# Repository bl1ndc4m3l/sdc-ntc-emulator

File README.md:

# SDC NTC emulator

A wireless room sensor for the **Honeywell Home (Resideo) Smile SDC** heating controller, without running a bus cable.

The Smile SDC normally regulates from the outdoor temperature only. Fed with a room temperature, it can also correct for the reference room ("room influence"). This board sits next to the controller and **emulates an NTC 20 kΩ room sensor (type RF 20)** on one of the SDC's variable inputs. The real room temperature comes over Wi-Fi from Home Assistant.

```
 room sensor ──Wi-Fi──▶ Home Assistant ──ESPHome API──▶ ESP32-S3 ──I2C (isolated)──▶ AD5272 rheostat ──▶ SDC input VE1
                                                           │                         + 18.2 kΩ series
                                                           └── fail-safe relay: without power the SDC sees a fixed 24.9 kΩ
```

Main design points:
- **Galvanically isolated** from the SDC: an I2C isolator and an isolated DC/DC supply. So USB debugging is possible while the board is installed.
- **Fail-safe by hardware:** when the ESP32 is unpowered, crashed or rebooting, a non-latching relay connects a fixed resistor at the room setpoint. The controller then runs weather-compensated, as it did before, without a fault code.
- **Mains-free PCB:** 5 V from a USB-C charger or an external 5 V supply.

## Status

| Part | State |
|---|---|
| PCB | **rev 4 designed**: ERC/DRC clean, isolation gap ≥ 1.14 mm checked. **Not yet manufactured or tested.** |
| Firmware | **not written yet**, specified in the design notes |
| Field measurements | done on an SDC3-40PM, software V3.3: input VE1, bias voltage, measuring current, display offset |
| Open | DevKit clone USB diode check, SDC service-port pinout, firmware |

This is a work in progress. Treat the board as untested until a built and commissioned unit is reported here.

## ⚠ Safety

- The SDC carries **230 V** (burner, pumps, mixer) on terminals X7–X10. Connect **only** to the low-voltage sensor terminals: VE1 = X6-6, sensor GND = X5-2…12. **Never use X5-1**: that is the T2B data bus.
- Switch the controller off before opening it. Any mains wiring (only needed with a built-in supply such as the RAC03) must be done by a qualified person.
- Modifying the heating installation may affect its warranty. You do this at your own risk.

## Repository layout

| Path | Contents |
|---|---|
| [`docs/design-notes.md`](docs/design-notes.md) | The design record: measurements, circuit decisions, failure modes, firmware specification, SDC parameter setup |
| [`pcb/`](pcb/README.md) | KiCad 9 project, generator scripts, and production files (Gerbers, BOM, DigiKey/Mouser order files, schematic PDF) |
| [`firmware/`](firmware/README.md) | ESPHome firmware for the ESP32-S3 (pin map and plan; not written yet) |
| [`LICENSES/`](LICENSES) | Licence texts, see [Licence](#licence) |

## Building one

1. **Board:** upload `pcb/production/sdc-ntc-emulator-jlcpcb-gerbers.zip` to JLCPCB, or any other fab: 2 layers, 1.6 mm, standard rules. Check the points under ["Verify before ordering"](pcb/README.md#verify-before-ordering) first.
2. **Parts:** import `pcb/production/sdc-ntc-emulator-digikey-order-3x.csv` (DigiKey BOM Manager) or `…-mouser-order-3x.csv` (Mouser BOM Tool). Both are for 3 boards. Also needed: an **ESP32-S3-DevKitC-1 (N16R8)** on sockets, and a 5 V ≥ 2 A USB-C charger.
3. **Assembly and bench checks:** see [pcb/README.md](pcb/README.md#assembly). Everything is hand-solderable; the AD5272 (MSOP-10) is the only fine-pitch part.
4. **Firmware:** see [firmware/](firmware/README.md). Until it exists, the board keeps the relay off and the SDC sees the fixed fail-safe resistance.
5. **Controller setup:** assign the input (HYDRAULIC parameter 08 = 31 for mixed heating circuit 1), then enable room influence moderately. See ["Setup on the SDC controller"](docs/design-notes.md#setup-on-the-sdc-controller).

### Regenerating the KiCad files

The schematic, PCB and all production files are generated from `pcb/tools/design.py` by `pcb/tools/build.py`. This needs **KiCad 9.0** and Python 3. See ["How the files are made"](pcb/README.md#how-the-files-are-made) for the environment variables on non-Windows systems.

### Datasheets

The manuals and datasheets are copyrighted and **not included**. Get them from the manufacturers:
- Resideo SDC3-40PM: service manual EN2H-0221GE51, operating instructions EN2H-0220GE51, parameter list EN0B-0565GE51 (all R1020). The terminal plan is in the German product information GE0H-0405GE51.
- Analog Devices AD5272. Texas Instruments ISO1540 and ISO7721. Omron G5V-2. Gaptec 1S4E_1U. ST L78L05.
- Espressif ESP32-S3, ESP32-S3-WROOM-1, ESP32-S3-DevKitC-1 V1.1 schematic.
- Recom RAC03-SER/277, only if you use the built-in mains supply.

## Licence

- **Hardware** (`pcb/` except `pcb/tools/`, and `docs/`): [CERN-OHL-S-2.0](LICENSES/CERN-OHL-S-2.0.txt).
- **Software** (`pcb/tools/`, `firmware/`): [GPL-3.0-or-later](LICENSES/GPL-3.0-or-later.txt).

See [LICENSE](LICENSE) for details. Honeywell Home, Smile and Resideo are trademarks of their respective owners. This project is not affiliated with or endorsed by them.

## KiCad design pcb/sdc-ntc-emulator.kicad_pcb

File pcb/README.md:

# SDC NTC emulator PCB (rev 4)

KiCad 9 project for the wireless room sensor of the Smile SDC3-40PM, as described in
[docs/design-notes.md](../docs/design-notes.md). On the board:
- ESP32-S3 DevKit on sockets
- ISO1540 I2C isolator, Gaptec 1S4E_0509S1U isolated 9 V supply + L78L05, AD5272 digital rheostat
- Omron G5V-2 fail-safe relay with state sense
- reverse-polarity protection on the 5 V input
- isolated UART to the SDC service port
- power and relay LEDs, and an expansion header

2 layers, 104 × 76 mm, 4 × M3 holes.

## Status

| Check | Result |
|---|---|
| ERC | 0 errors, 0 warnings |
| DRC (incl. schematic parity) | 0 violations, 0 unconnected pads |
| Isolation gap ESP ↔ SDC side (`tools/check_isolation.py`) | **≥ 1.14 mm** copper to copper, both layers (required ≥ 1.0 mm); tightest spot between PS1 pins 2 and 3 |
| Gerbers + drill for JLCPCB | `production/sdc-ntc-emulator-jlcpcb-gerbers.zip` |
| BOM | `production/sdc-ntc-emulator-bom.csv` |
| Order files for 3 boards (`BOARDS` in `tools/design.py`) | DigiKey BOM Manager: `production/sdc-ntc-emulator-digikey-order-3x.csv` (with DigiKey part numbers), Mouser BOM Tool: `production/sdc-ntc-emulator-mouser-order-3x.csv` |

Rev 3 (Traco TMR 1-0511, never ordered) is tagged `pcb-rev3` in git.

### Changes from rev 3 (2026-10-04): cheaper isolated supply

PS1 cost €8.85 per board (TMR 1-0511, a third of the DigiKey order). Rev 4 replaces it with an unregulated 5 V → 9 V module and a linear regulator, ≈ €2.75 per board in total.

- **PS1 Gaptec 1S4E_0509S1U** (Gaptec 1S4E_1U datasheet, DigiKey 3182-1S4E_0509S1U-ND):
  - 5 V in, 9 V / 111 mA out, unregulated, 1000 VDC, 20 pF isolation capacitance.
  - SIP-4 (1 GND, 2 Vin, 3 −Vo, 4 +Vo), pin-compatible with the Traco TME 05xxS, so it uses KiCad's TME symbol and footprint.
  - No-load input current max 15 mA (TMR: 40 mA).
  - **Needs ≥ 10 % load (11 mA)** (datasheet section 3; the selection table says 0 mA, the text wins). Below that the output voltage is not specified.
- **U4 L78L05ACUTR** (SOT-89) makes VDD_ISO = 5 V from the 9 V rail.
  - 30 V max input, so the unregulated rail's light-load rise (max +10 % at 10 % load, plus input tolerance: ≈ 10.5 V worst case) is harmless.
  - ≈ 1.7 V dropout; the rail stays above ≈ 8.4 V at our load.
  - Its ≈ 4–6 mA quiescent current counts towards the PS1 minimum load.
- **R24 1.5 kΩ** preload on the 9 V rail (≈ 6–7 mA, ≤ 75 mW). With U4's own current and the VDD_ISO load (U1/U3 side 2, D2, pull-ups) the module sees ≈ 15–20 mA, above its 10 % minimum.
- **C12 10 µF 25 V X7R 1206** (same part as C9) at the module output / LDO input. 25 V/1206 because a 16 V 0805 loses most of its capacitance at 10 V DC bias.
- **Isolation gap 1.40 → 1.14 mm.** On the SIP-4, +Vin (pin 2) and −Vout (pin 3) are 2.54 mm apart. The pads are narrow ovals (1.4 × 2.2 mm, 1.0 mm drill), and the gap line runs midway between pins 2 and 3.
- **Supply budget:** ≈ 40–45 mA from the 5 V rail for the isolated side (TMR: ≈ 50 mA). Estimated, not measured.
- **Clear zone around PS1:** C2 sits left of the module, C12/C4/U4/R24/R7/D2 right of it. No part lies where either possible body orientation could cover it.
- **Silkscreen:** every part's reference is printed next to it, never under a part body, and clear of pads, vias and other text. The labels are placed by `place_refs()` in `tools/make_pcb.py`, and the build fails if one finds no spot. Value texts are not printed; R9/R10's descriptions are gone, and their values are in the BOM.
  - J6 moved up into the free strip at the left edge. Its signal names (3V3, IO2, IO1, GND) sit next to each pin, and R18–R21 have room for their labels.
  - R22/R23 lie flat and stacked next to J7; the dashed gap line now starts below them.
  - Third title line: "Made by bl1ndc4m3l, authored by Claudine".

### Changes from rev 2 (2026-09-30 / 2026-10-01)

- **Isolated supply: Traco TMR 1-0511 replaces the TEM 2-0511** (PS1; Traco TMR 1 datasheet).
  - **Straight gap:** SIP-6 with the input at one end (pin 1 −Vin, pin 2 +Vin) and the output at the other (pin 4 +Vout, pin 6 −Vout). Pin 3 is absent, so there are 3.6 mm of copper between pins 2 and 4. The isolation gap is now one straight line from the top edge through PS1, U1 and U3, plus one step around the relay contacts. The TEM's pinout put −Vin next to +Vout and forced a notch into the gap.
  - **Wider gap:** 1.15 → 1.40 mm.
  - **Regulated** ±1 %, **no minimum load**, so the R8 preload resistor is gone.
  - **No-load input current** 40 mA instead of 80 mA, which relieves the tight RAC03 budget.
  - **1500 VDC** isolation, 200 mA output (the SDC side needs ≈ 10–20 mA).
  - **Footprint and outline:** KiCad's `Converter_DCDC_TRACO_TMR-1-xxxx_Single_THT`; body 17 × 7.6 mm instead of 32 × 20 mm.
  - **No tracks under the body:** Traco says to avoid traces under the converter, so the router keeps tracks and vias out from under the body beyond the pin row.
- **C2** (input decoupling) 100 nF → 10 µF, against the 80 mA p-p reflected input ripple.
- **USB-C power input J7** (GCT USB4125-GF-A-0190, power only):
  - It sits in parallel with J3, in front of Q2.
  - 5.1 kΩ on each CC line, so any USB-C charger supplies 5 V. There is no USB Power Delivery, so never more.
  - J3 shifted 1.9 mm left; Q2 and C1 moved down to make room.
- **SDC service port J5** (JST XH, 4-pin, bottom edge):

  | J5 pin | Signal | Notes |
  |---|---|---|
  | 1 | GND_ISO | |
  | 2 | RX | into the board; connect to the SDC's TX |
  | 3 | TX | out of the board; connect to the SDC's RX |
  | 4 | 5 V | VDD_ISO (since rev 4 from U4), through R17 |

  - **Isolated:** the 9600 baud UART goes through U3 (ISO7721). It sits across the gap like U1, so the port is on the SDC side of the barrier.
  - **ESP pins:** GPIO6 = RX, GPIO7 = TX.
  - **R15/R16 (1 kΩ):** protect the lines if the pinout turns out wrong, for example two outputs driving against each other.
  - **Idle state:** U3's outputs default high (UART idle) when its input is open, for example while the ESP boots or with no cable connected.
  - **The SDC socket's pinout is not measured yet**, see "Service port" below.
- **Power LED D3** (green) on +5 V after Q2, so it also shows that the input polarity is right.
- **Relay LED D4** (yellow): across the coil, not driven by a GPIO, so it shows whether the coil really has power.
- **Expansion header J6** (2.54 mm, left edge): 3V3, GPIO2, GPIO1, GND.
  - 100 Ω series resistors R18/R19.
  - Optional 4.7 kΩ pull-ups R20/R21 (DNP) for I2C or 1-Wire.
  - GPIO1/2 are ADC1-capable and have no strapping function.
- Extra 5 V load: ≈ 3 mA for the LEDs, plus U3 and whatever is plugged into J5 (fed via PS1). This is negligible against the Wi-Fi peaks.

### Changes from rev 1 (independent review, 2026-09-30)

- **Isolation gap** 0.40 mm → 1.15 mm. Rev 1's documentation wrongly claimed ≥ 1 mm. Fixes:
  - oval TEM pads, 1.24 mm between +Vout and −Vin
  - ≥ 1.2 mm between the domain outlines
  - the router keeps whole tracks inside their domain
  - a new build check measures the real gap
- **Relay state sense** R11/R12 → GPIO5 (LOW = coil energised).
- **Reverse-polarity P-FET** Q2 in the 5 V input.
- **Resistors:**
  - R9 (R_series) 15.0 → 18.2 kΩ: floor ≈ 27 °C even with the AD5272 unpowered or shorted.
  - R10 (R_failsafe) 24.3 → 24.9 kΩ, which accounts for the SDC's +0.5 K offset.
  - R1/R2 4.7 → 2.7 kΩ: ISO1540 side-1 sink current.
- **Layout and footprints:**
  - C3/C5 moved next to the ISO1540 supply pins.
  - Relay holes 1.0 mm, as Omron recommends.
  - The AD5272 fan-out now has no wide tracks, no vias and no signal tracks under the body. A and VSS are tied to GND by a short trace under the body, under solder mask.
  - Silkscreen text ≥ 1.0 mm.
  - "GND X5-2..12" marking, because X5-1 is the SDC data bus.

## Verify before ordering

1. **DevKit row spacing: 25.1 mm** (`DEVKIT_ROWS` in `tools/make_pcb.py`, measured: outer 25.6 / inner 24.6 mm).
   - The pinout is confirmed from a photo: it is identical to the official DevKitC-1.
   - Solder the sockets with the DevKit plugged in.
   - The clone is ~56.6 × 27.7 mm. Its module antenna overhangs the DevKit edge by ~7 mm at the pin-1 end; the no-copper area covers that.
   - DevKit J3 pin 1 (GND) is intentionally not connected.
   - On the silkscreen the DevKit headers are "DK-J1"/"DK-J3", to tell them apart from the 5 V terminal J3.
2. **PS1 footprint.** It is KiCad's Traco TME SIP-4 footprint with narrow oval pads (pins 1–4 on a 2.54 mm grid, 1.0 mm holes, as in the Gaptec drawing). The pin-1 marking (square pad, left) must be the GND (−Vin) end.
   - **Body side does not matter:** the pin row sits ≈ 1–1.7 mm from one face of the 6 mm deep body. No other part is placed within 5.6 mm of the pin row on either side, or within 6.3 mm of its centre along the row (`PS1_BODY_MAX` in `tools/make_pcb.py`, checked by the build). So the module fits whichever way its body extends.
   - **After assembly, measure** the 9 V rail at C12 (expect ≈ 9–10.5 V) and VDD_ISO at C4 (5 V ±4 %).
3. **Terminal blocks.** The wire entries should face the board edge: J3 (5 V in) the top edge, J4 (to SDC) the right edge. This follows from KiCad's footprint graphics; confirm in the 3D view.
4. **R10 (R_failsafe) = 24.9 kΩ** assumes an SDC day setpoint of 21 °C (displayed). For another setpoint, pick the value from the NTC table in the [design notes](../docs/design-notes.md#ntc-20-resistance-from-service-manual-en2h-0221ge51-r1020-ch-821), taking the +0.5 K display offset into account. It is a through-hole part, so it is easy to swap.

## Ordering at JLCPCB (bare board, hand soldering)

Upload the zip. Defaults are fine: 2 layers, 1.6 mm FR-4, 1 oz copper, HASL or ENIG, any colour. No assembly service needed.

Smallest features, all within JLC's standard capabilities:
- **Clearance:** ≥ 0.20 mm everywhere except at the AD5272 MSOP-10 (rule there: 0.13 mm; actual: 0.15 mm pad gap, and one via 0.175 mm from a track at its courtyard edge). Verified by a DRC run with 0.20 mm netclass clearance.
- **Tracks:** 0.25 mm.
- **Vias:** 0.8/0.4 mm, tented.

## Assembly

Order:
1. SMD first:
   - U2 (MSOP-10) first, with flux and a fine tip;
   - then U1, U3, Q1, Q2, D1 and the 0805/1206 parts;
   - C9 sits under the DevKit;
   - LEDs: the cathode mark faces GND (D3) or the relay coil (D4).
2. The low THT parts (R9, R10).
3. The sockets, relay, PS1, C1, the terminals, J5 and J6.

**USB-C J7** (GCT USB4125-GF-A-0190):
- Solder the 6 SMD contacts first, with flux. The two CC pads in the middle are only 0.3 mm apart.
- Then solder the 4 shell pegs from the bottom.
- The two 5.1 kΩ resistors right behind it (references not printed) are R22 (left, CC1) and R23 (right, CC2).

Left edge, next to J6 (references not printed), top to bottom:

| Position | Part | Value |
|---|---|---|
| 1 | R21 | 4.7 kΩ pull-up GPIO1, DNP |
| 2 | R20 | 4.7 kΩ pull-up GPIO2, DNP |
| 3 | R18 | 100 Ω, GPIO2 |
| 4 | R19 | 100 Ω, GPIO1 |

Notes:
- **D2** lights when the isolated side has power.
- Relay K1: both poles are wired in parallel on purpose. Two gold contacts are more reliable at µA currents.
- **Before the first power-up, check with an ohmmeter:**
  - J4 VE1 to J4 GND = R10 (24.9 kΩ) with the relay off.
  - There must be no connection at all between the ESP side GND (J3 −) and the SDC side GND (J4 GND).
- **Wiring to the SDC:** J4 GND to **X5-2…12, never X5-1** (T2B data bus).

Not on the PCB: the ESP32-S3 DevKit, the RAC03 with its fuse and mains terminals (separate section of the enclosure), 4 × M3 spacers.

## 5 V supply alternatives (RAC03 is end-of-life) and kit package

There are two 5 V inputs, wired in parallel in front of Q2:
- **J7, USB-C** (top edge, next to J3): any USB-C charger.
  - The board is a plain power sink, with 5.1 kΩ on each CC line (R22/R23). There is no USB Power Delivery negotiation, so a charger never supplies more than 5 V.
  - Use a charger rated **5 V ≥ 2 A**. A PC USB port (0.5–0.9 A) is too weak for the Wi-Fi peaks.
- **J3, screw terminal:** any regulated 5 V supply with wires. Q2 protects against swapped polarity, not against overvoltage.

**Use only one of J3 and J7.** Both feed the same node, so two supplies connected at the same time would drive each other. The DevKit's own USB ports are a third route; see the open diode check in the [design notes](../docs/design-notes.md#open-points). Powering the board from the DevKit's USB port instead is not recommended: the DevKit's VBUS diode drops ≈ 0.4 V, which leaves PS1 at the edge of its 4.5 V minimum.

| Option | Part | Rating | Mains wiring by the user | Notes |
|---|---|---|---|---|
| **Kit default** | any certified **USB-C charger** into J7 | 5 V ≥ 2 A | **none** | Every buyer has one. With a cable it reaches about 3–4× the RAC03's current, which ends the tight Wi-Fi peak budget. Needs a socket near the SDC. |
| Plug-in adapter with wires | Mean Well **SGA12E05-P1J** | 5 V / 2.4 A, 12 W, EU plug | **none** | CE/CB certified, 5.5/2.1 mm barrel plug, centre positive. Connect it into J3 with a DC-jack-to-screw-terminal pigtail, or cut the plug off. |
| Same concept as the RAC03 | Recom **RAC05-05SK/277/W** | 5 V / 1 A, 5 W, 80–305 VAC, wire leads | yes (qualified person) | Potted module with flying leads, so the PCB stays mains-free. Needs a slow-blow fuse and an enclosure with a separate mains section. |
| Control cabinet / DIN rail | Mean Well **HDR-15-5** | 5 V / 2.4 A, 12 W, 17.5 mm wide | yes (qualified person) | Screw terminals, < 0.3 W no-load. Fits next to other DIN-rail equipment in the boiler room. |

**Selling as a kit** (bare PCB + parts, unassembled):
- Included: PCB and all parts from the order file. Power comes from the buyer's own USB-C charger, so the buyer never touches mains.
- Not included: the ESP32-S3 DevKit (the buyer brings it, or offer it as an option) and the enclosure.
- Documentation: this README and the design notes, with the wiring to the SDC (X5-2…12, never X5-1) and the service-port pinout once it is measured.

## Bench checks after assembly

- **VDD_ISO** (C4, against J4 GND): 5.0 V ±1 % (4.95–5.05 V).
- **I2C on the ESP side:** look at SDA/SCL with a scope. The ISO1540's low level (≤ 0.8 V) is close to the ESP32-S3's VIL (0.825 V).
- **Relay sense:** GPIO5 must read HIGH with the relay off and LOW with it on. D4 must light exactly when GPIO5 is LOW.
- **USB-C input:** with a charger on J7, D3 lights and +5 V (C1) reads ≈ 5 V. With the board unpowered, CC1 and CC2 each measure 5.1 kΩ to GND.
- **Service port idle:** with nothing on J5, GPIO6 reads HIGH, and J5-3 (TX) measures ≈ 5 V against J5-1.

## Service port (J5): before connecting the SDC

The SDC has a 6-pin socket (≈ 1.0 mm pitch) behind the small flap above the day/night buttons. It carries a proprietary framed protocol at 9600 baud, 5 V logic:
- frames end with `21 0A 0A`;
- checksum CRC-16/KERMIT;
- a decoder from an earlier sniffing project exists.

**Its pinout is not known yet.** Measure before connecting anything:

1. With the SDC powered, measure every pin against **X5-2** (sensor GND):
   - GND reads 0 V;
   - a supply pin reads a steady ≈ 5 V;
   - the SDC's TX idles at ≈ 5 V and flickers on a scope or logic analyser;
   - the SDC's RX idles high, but stays quiet.
2. **With the SDC off, check continuity from the port's GND to X5-2.** J5-1 is GND_ISO, which is the same net as J4 GND (X5). Only connect J5-1 if the port GND and X5 are the same potential. If they are not, J5 would tie two different grounds together through the board. That needs a separate isolated domain for the port (a board change).
3. If the port has its own 5 V pin, **remove R17**. Otherwise PS1 and the SDC's supply would drive the same line. With R17 fitted, J5-4 is a 5 V supply for an adapter at the SDC end.
4. Wiring:
   - J5-2 (RX) to the SDC's **TX**;
   - J5-3 (TX) to the SDC's **RX**.
   - Start listen-only: leave J5-3 unconnected, or keep the ESPHome UART `tx_pin` unset, until the protocol is understood.
5. Mating plug: JST XHP-4. Keep the fragile 1.0 mm adapter at the SDC end: a 3D-printed insert that fills the flap recess, carrying a 1.0 mm pin header or pogo pins. Add strain relief to the housing.

## How the files are made

Everything is generated from `tools/design.py` (parts, values, footprints, nets) by:

```
python tools/build.py   # footprints -> schematic -> ERC -> netlist -> PCB -> DRC -> isolation check -> Gerbers/BOM/renders
```

Requirements:
- **KiCad 9.0** (the committed outputs were made with 9.0.7). `tools/make_pcb.py` and `tools/check_isolation.py` run in KiCad's own Python, which provides `pcbnew` and `numpy`.
- **Python 3** for `build.py`, `make_schematic.py` and `make_footprints.py` (standard library only).
- The scripts default to the Windows install in `C:\Program Files\KiCad\9.0`. Elsewhere, set:

  | Variable | Points to | Example (Linux) |
  |---|---|---|
  | `KICAD_CLI` | `kicad-cli` | `/usr/bin/kicad-cli` |
  | `KICAD_PYTHON` | a Python that can `import pcbnew` (needs `numpy`) | `python3` |
  | `KICAD9_SYMBOL_DIR` | KiCad's standard symbol libraries | `/usr/share/kicad/symbols` |
  | `KICAD9_FOOTPRINT_DIR` | KiCad's standard footprint libraries | `/usr/share/kicad/footprints` |

  On Windows with KiCad installed elsewhere, `KICAD_BIN` (the folder with `kicad-cli.exe` and `python.exe`) is enough for the first two.

- `tools/make_schematic.py`: writes `sdc-ntc-emulator.kicad_sch` from `design.py` (net labels at every pin).
- `tools/make_pcb.py` (runs in KiCad's Python): placement, routing, pours, keep-outs and silkscreen.
  - The router is a small grid A* router.
  - Each net is kept inside its own domain outline (ESP side or isolated SDC side), including half its track width.
  - The AD5272 fan-out is routed in a fixed order, with protected exit corridors for each 0.5 mm-pitch pin.
  - Placement lives in `PLACEMENT`, domain outlines in `ESP_POLY`/`ISO_POLY`.
- `tools/check_isolation.py` (KiCad Python): merges all copper of each domain per layer and measures the true minimum gap. The build fails below 1.0 mm.
- `tools/make_footprints.py`: the TEM 2 footprint (no longer used since PS1 is a TMR 1; kept with its symbol in `lib/` in case the TEM 2-0511 on hand is used for something else).

**Rebuilding overwrites the `.kicad_sch` and `.kicad_pcb`.** Make changes in `design.py`/`make_pcb.py` and rebuild. If you prefer to continue by hand in KiCad, stop using the scripts from that point on, and run `check_isolation.py` after your edits.

**Known limitation:** `kicad-cli` ignores `sdc-ntc-emulator.kicad_dru`; even a deliberately broken rule gives no error. That is why:
- the global minimum clearance is 0.13 mm, needed for the MSOP-10 pad gaps;
- the isolation gap is checked by `check_isolation.py` instead of a DRC rule.

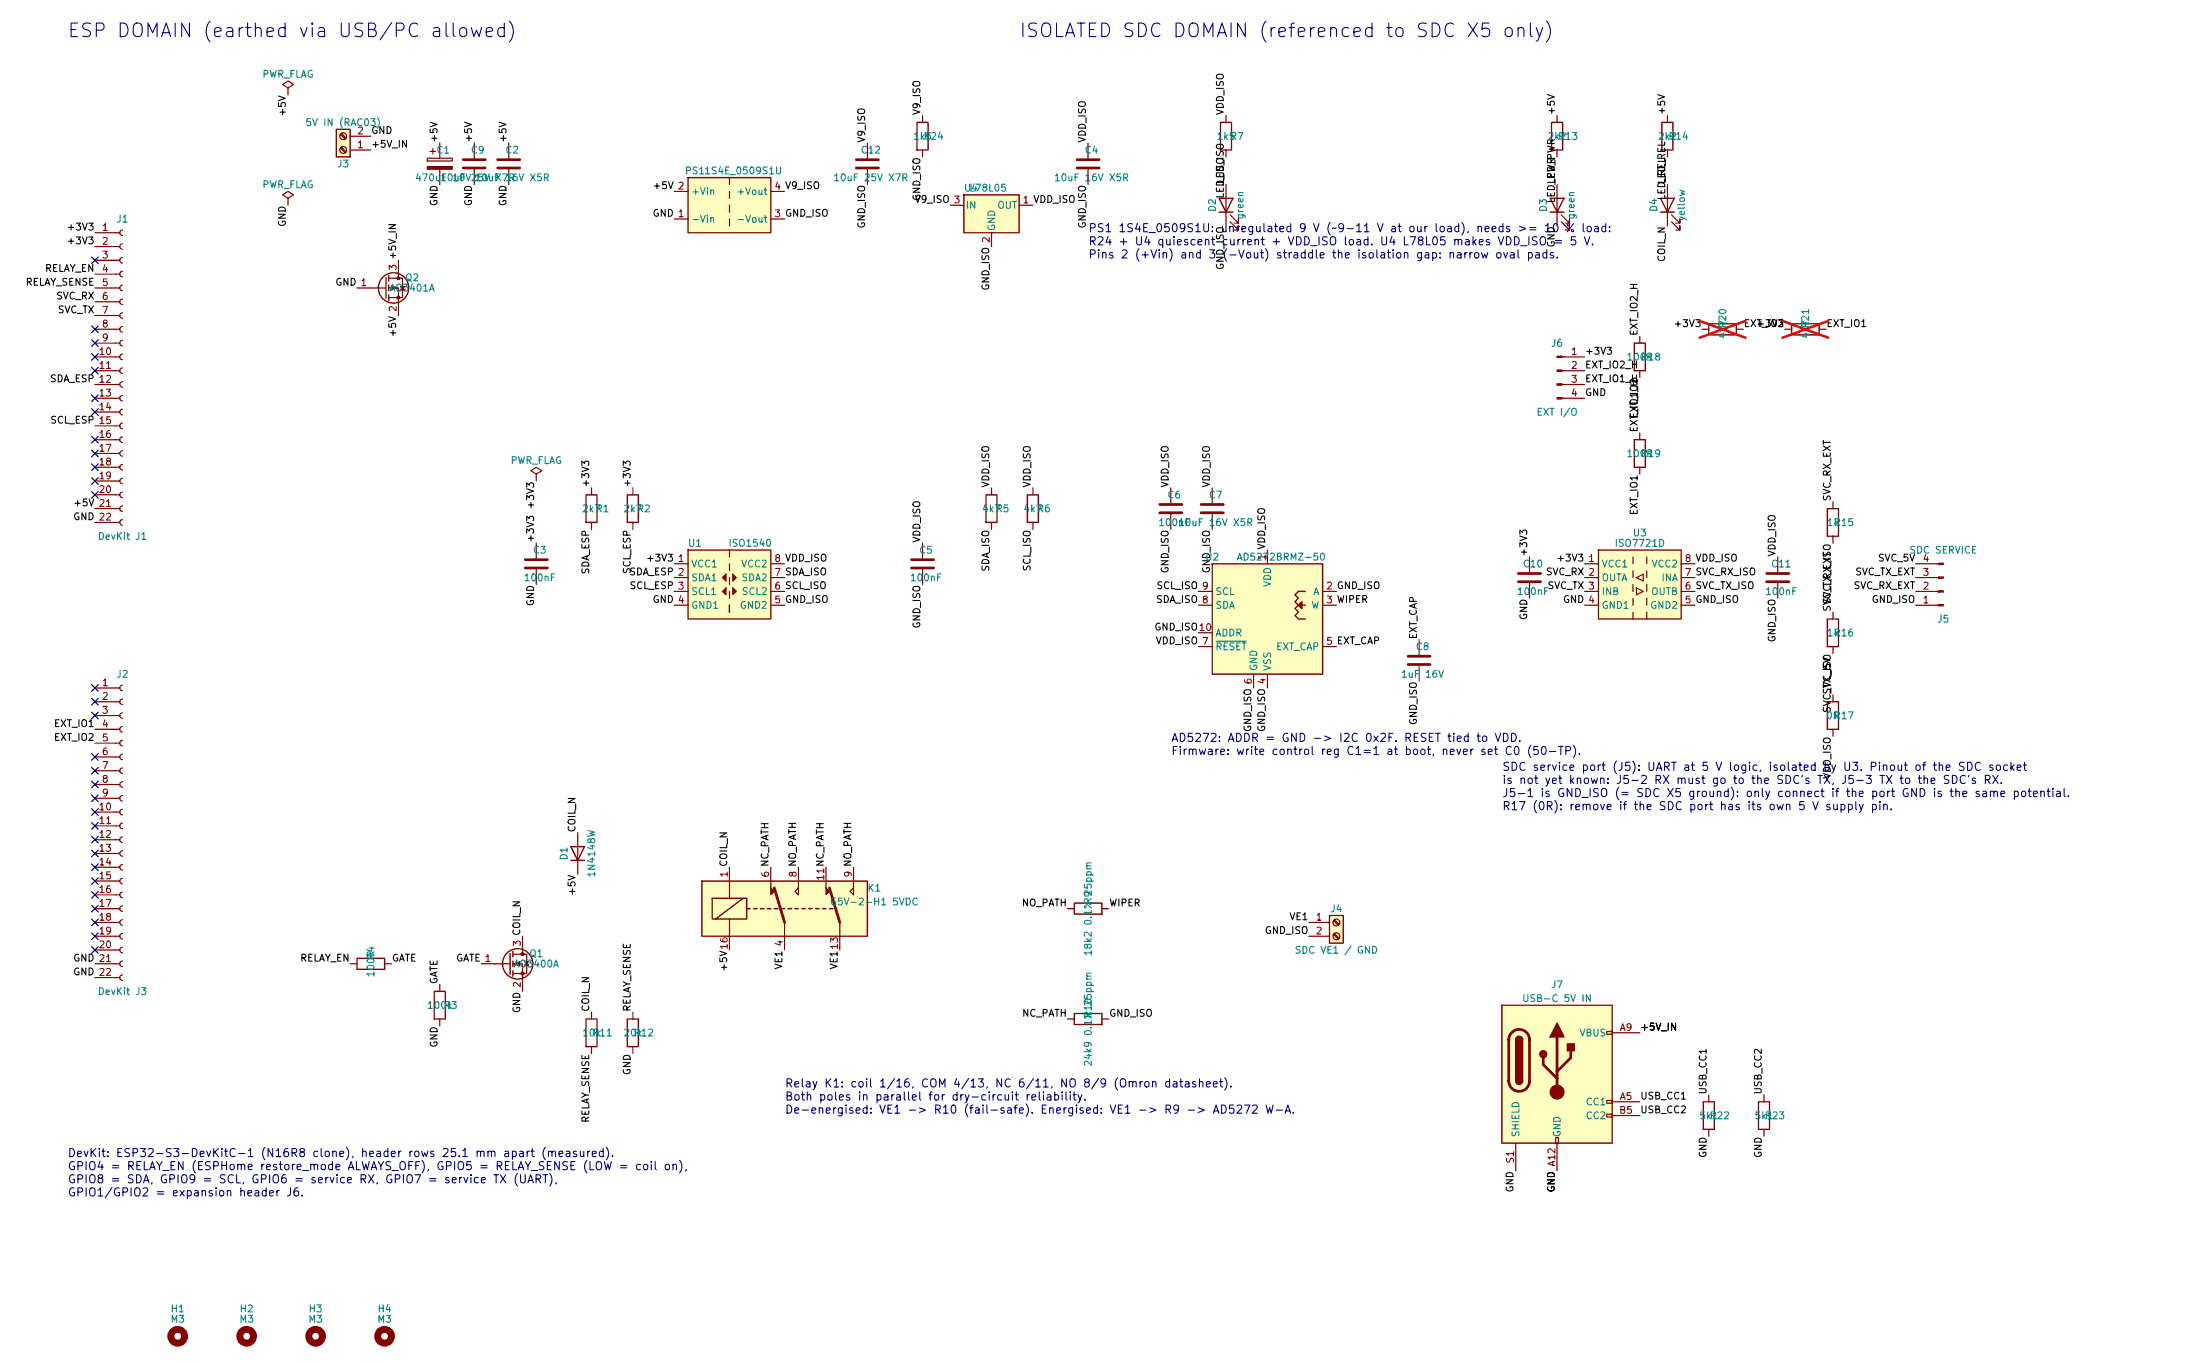
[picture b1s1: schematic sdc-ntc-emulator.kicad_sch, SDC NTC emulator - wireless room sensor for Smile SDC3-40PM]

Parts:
C1: 470uF 10V; CP_Radial_D8.0mm_P3.50mm; MPN EEU-FR1A471
C2, C4, C7: 10uF 16V X5R; C_0805_2012Metric_Pad1.18x1.45mm_HandSolder; MPN CC0805KRX5R7BB106
C3, C5, C6, C10, C11: 100nF; C_0805_2012Metric_Pad1.18x1.45mm_HandSolder; MPN CL21B104KBCNNNC
C8: 1uF 16V; C_0805_2012Metric_Pad1.18x1.45mm_HandSolder; MPN GRM219R71E105KA88D
C9, C12: 10uF 25V X7R; C_1206_3216Metric_Pad1.33x1.80mm_HandSolder; MPN GRM31CR71E106MA12L
D1: 1N4148W; D_SOD-123; MPN 1N4148W-7-F
D2, D3: green; LED_0805_2012Metric_Pad1.15x1.40mm_HandSolder; MPN LTST-C171GKT
D4: yellow; LED_0805_2012Metric_Pad1.15x1.40mm_HandSolder; MPN LTST-C171YKT
H1, H2, H3, H4: M3; MountingHole_3.2mm_M3
J1: DevKit J1; PinSocket_1x22_P2.54mm_Vertical; MPN PPTC221LFBN-RC
J2: DevKit J3; PinSocket_1x22_P2.54mm_Vertical; MPN PPTC221LFBN-RC
J3: 5V IN (RAC03); TerminalBlock_Phoenix_MKDS-1,5-2-5.08_1x02_P5.08mm_Horizont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; MPN 1715721
J4: SDC VE1 / GND; TerminalBlock_Phoenix_MKDS-1,5-2-5.08_1x02_P5.08mm_Horizont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; MPN 1715721
J5: SDC SERVICE; JST_XH_B4B-XH-A_1x04_P2.50mm_Vertical; MPN B4B-XH-A(LF)(SN)
J6: EXT I/O; PinHeader_1x04_P2.54mm_Vertical; MPN 61300411121
J7: USB-C 5V IN; USB_C_Receptacle_GCT_USB4125-xx-x-0190_6P_TopMnt_Horizontal; MPN USB4125-GF-A-0190
K1: G5V-2-H1 5VDC; Relay_DPDT_Omron_G5V-2; MPN G5V-2-H1 DC5
PS1: 1S4E_0509S1U; Converter_DCDC_TRACO_TME_03xxS_05xxS_12xxS_Single_THT; MPN 1S4E_0509S1U
Q1: AO3400A; SOT-23; MPN AO3400A
Q2: AO3401A; SOT-23; MPN AO3401A
R1, R2: 2k7; R_0805_2012Metric_Pad1.20x1.40mm_HandSolder; MPN RC0805FR-072K7L
R3: 100k; R_0805_2012Metric_Pad1.20x1.40mm_HandSolder; MPN RC0805FR-07100KL
R4, R18, R19: 100R; R_0805_2012Metric_Pad1.20x1.40mm_HandSolder; MPN RC0805FR-07100RL
R5, R6: 4k7; R_0805_2012Metric_Pad1.20x1.40mm_HandSolder; MPN RC0805FR-074K7L
R7, R24: 1k5; R_0805_2012Metric_Pad1.20x1.40mm_HandSolder; MPN RC0805FR-071K5L
R9: 18k2 0.1% 25ppm; R_Axial_DIN0207_L6.3mm_D2.5mm_P10.16mm_Horizontal; MPN YR1B18K2CC
R10: 24k9 0.1% 25ppm; R_Axial_DIN0207_L6.3mm_D2.5mm_P10.16mm_Horizontal; MPN YR1B24K9CC
R11: 10k; R_0805_2012Metric_Pad1.20x1.40mm_HandSolder; MPN RC0805FR-0710KL
R12: 20k; R_0805_2012Metric_Pad1.20x1.40mm_HandSolder; MPN RMCF0805FT20K0
R13, R14: 2k2; R_0805_2012Metric_Pad1.20x1.40mm_HandSolder; MPN RC0805FR-072K2L
R15, R16: 1k; R_0805_2012Metric_Pad1.20x1.40mm_HandSolder; MPN RC0805FR-071KL
R17: 0R; R_0805_2012Metric_Pad1.20x1.40mm_HandSolder; MPN RC0805JR-070RL
R20, R21: 4k7; R_0805_2012Metric_Pad1.20x1.40mm_HandSolder; MPN RC0805FR-074K7L; not fitted
R22, R23: 5k1; R_0805_2012Metric_Pad1.20x1.40mm_HandSolder; MPN CR0805-FX-5101ELF
U1: ISO1540; SOIC-8_3.9x4.9mm_P1.27mm; MPN ISO1540DR
U2: AD5272BRMZ-50; MSOP-10_3x3mm_P0.5mm; MPN AD5272BRMZ-50
U3: ISO7721D; SOIC-8_3.9x4.9mm_P1.27mm; MPN ISO7721DR
U4: L78L05; SOT-89-3; MPN L78L05ACUTR

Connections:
/+3V3: C3.1, C10.1, J1.1, J1.2, J6.1, R1.1, R2.1, R20.1, R21.1, U1.1 (VCC1), U3.1 (VCC1)
/+5V: C1.1, C2.1, C9.1, D1.1 (K), J1.21, K1.16, PS1.2 (+Vin), Q2.2 (S), R13.1, R14.1
/+5V_IN: J3.1, J7.A9 (VBUS), J7.B9 (VBUS), Q2.3 (D)
/COIL_N: D1.2 (A), D4.1 (K), K1.1, Q1.3 (D), R11.1
/EXT_CAP: C8.1, U2.5 (EXT_CAP)
/EXT_IO1: J2.4, R19.2, R21.2
/EXT_IO1_H: J6.3, R19.1
/EXT_IO2: J2.5, R18.2, R20.2
/EXT_IO2_H: J6.2, R18.1
/GATE: Q1.1 (G), R3.1, R4.2
/GND: C1.2, C2.2, C3.2, C9.2, C10.2, D3.1 (K), J1.22, J2.21, J2.22, J3.2, J6.4, J7.A12 (GND), J7.B12 (GND), J7.S1 (SHIELD), PS1.1 (-Vin), Q1.2 (S), Q2.1 (G), R3.2, R12.2, R22.2, R23.2, U1.4 (GND1), U3.4 (GND1)
/GND_ISO: C4.2, C5.2, C6.2, C7.2, C8.2, C11.2, C12.2, D2.1 (K), J4.2, J5.1, PS1.3 (-Vout), R10.2, R24.2, U1.5 (GND2), U2.2 (A), U2.4 (VSS), U2.6 (GND), U2.10 (ADDR), U3.5 (GND2), U4.2 (GND)
/LED_ISO: D2.2 (A), R7.2
/LED_PWR: D3.2 (A), R13.2
/LED_REL: D4.2 (A), R14.2
/NC_PATH: K1.6, K1.11, R10.1
/NO_PATH: K1.8, K1.9, R9.1
/RELAY_EN: J1.4, R4.1
/RELAY_SENSE: J1.5, R11.2, R12.1
/SCL_ESP: J1.15, R2.2, U1.3 (SCL1)
/SCL_ISO: R6.2, U1.6 (SCL2), U2.9 (SCL)
/SDA_ESP: J1.12, R1.2, U1.2 (SDA1)
/SDA_ISO: R5.2, U1.7 (SDA2), U2.8 (SDA)
/SVC_5V: J5.4, R17.1
/SVC_RX: J1.6, U3.2 (OUTA)
/SVC_RX_EXT: J5.2, R15.1
/SVC_RX_ISO: R15.2, U3.7 (INA)
/SVC_TX: J1.7, U3.3 (INB)
/SVC_TX_EXT: J5.3, R16.1
/SVC_TX_ISO: R16.2, U3.6 (OUTB)
/USB_CC1: J7.A5 (CC1), R22.1
/USB_CC2: J7.B5 (CC2), R23.1
/V9_ISO: C12.1, PS1.4 (+Vout), R24.1, U4.3 (IN)
/VDD_ISO: C4.1, C5.1, C6.1, C7.1, C11.1, R5.1, R6.1, R7.1, R17.2, U1.8 (VCC2), U2.1 (VDD), U2.7 (~RESET), U3.8 (VCC2), U4.1 (OUT)
/VE1: J4.1, K1.4, K1.13
/WIPER: R9.2, U2.3 (W)

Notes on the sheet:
ESP DOMAIN (earthed via USB/PC allowed)
ISOLATED SDC DOMAIN (referenced to SDC X5 only)
DevKit: ESP32-S3-DevKitC-1 (N16R8 clone), header rows 25.1 mm apart (measured). GPIO4 = RELAY_EN (ESPHome restore_mode ALWAYS_OFF), GPIO5 = RELAY_SENSE (LOW = coil on), GPIO8 = SDA, GPIO9 = SCL, GPIO6 = service RX, GPIO7 = service TX (UART), GPIO1/GPIO2 = expansion header J6.
SDC service port (J5): UART at 5 V logic, isolated by U3. Pinout of the SDC socket is not yet known: J5-2 RX must go to the SDC's TX, J5-3 TX to the SDC's RX. J5-1 is GND_ISO (= SDC X5 ground): only connect if the port GND is the same potential. R17 (0R): remove if the SDC port has its own 5 V supp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
Relay K1: coil 1/16, COM 4/13, NC 6/11, NO 8/9 (Omron datasheet). Both poles in parallel for dry-circuit reliability. De-energised: VE1 -> R10 (fail-safe). Energised: VE1 -> R9 -> AD5272 W-A.
AD5272: ADDR = GND -> I2C 0x2F. RESET tied to VDD. Firmware: write control reg C1=1 at boot, never set C0 (50-TP).
PS1 1S4E_0509S1U: unregulated 9 V (~9-11 V at our load), needs >= 10 % load: R24 + U4 quiescent current + VDD_ISO load. U4 L78L05 makes VDD_ISO = 5 V. Pins 2 (+Vin) and 3 (-Vout) straddle the isolation gap: narrow oval pads.

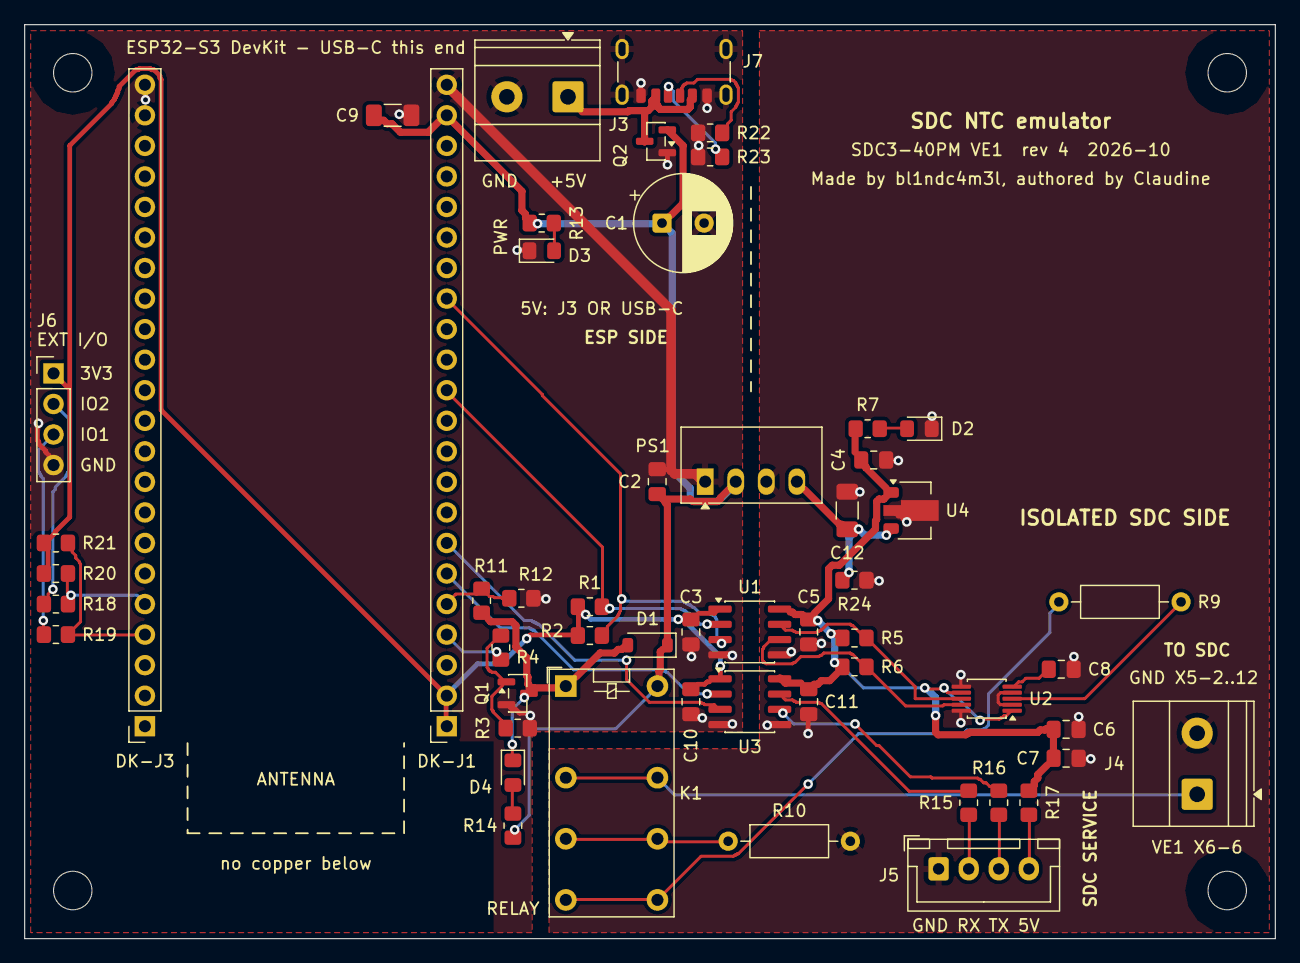
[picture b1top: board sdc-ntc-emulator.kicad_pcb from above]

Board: 2 copper layers, 104.0 x 76.0 mm, 58 parts (0 on the bottom side), 36 nets.

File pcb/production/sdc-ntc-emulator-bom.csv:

Qty,References,Value,Footprint,Purpose,Fit
1,C1,470uF 10V,CP_Radial_D8.0mm_P3.50mm,5 V bulk for Wi-Fi TX peaks,fit
3,C2 C4 C7,10uF 16V X5R,C_0805_2012Metric_Pad1.18x1.45mm_HandSolder,PS1 input decoupling (datasheet: 4.7 uF); U4 output buffer; U2 VDD decoupling,fit
5,C3 C10 C5 C6 C11,100nF,C_0805_2012Metric_Pad1.18x1.45mm_HandSolder,U1 VCC1 decoupling; U3 VCC1 decoupling; U1 VCC2 decoupling; U2 VDD decoupling; U3 VCC2 decoupling,fit
1,C8,1uF 16V,C_0805_2012Metric_Pad1.18x1.45mm_HandSolder,AD5272 EXT_CAP (>= 7 V rating),fit
2,C9 C12,10uF 25V X7R,C_1206_3216Metric_Pad1.33x1.80mm_HandSolder,"Low-ESR ceramic parallel to C1: RAC03 ripple, fast Wi-Fi current edges; PS1 output / U4 input (datasheet: 4.7 uF, max 1000 uF); 25 V 1206 for DC-bias derating at ~10 V",fit
1,D1,1N4148W,D_SOD-123,Flyback diode,fit
2,D3 D2,green,LED_0805_2012Metric_Pad1.15x1.40mm_HandSolder,5 V present (after the reverse-polarity FET); VDD_ISO present,fit
1,D4,yellow,LED_0805_2012Metric_Pad1.15x1.40mm_HandSolder,Relay coil energised (parallel to the coil: shows the real coil state),fit
1,J1,DevKit J1,PinSocket_1x22_P2.54mm_Vertical,ESP32-S3-DevKitC-1 header J1 (3V3/GPIO4-9/5V/GND),fit
1,J2,DevKit J3,PinSocket_1x22_P2.54mm_Vertical,"ESP32-S3-DevKitC-1 header J3 (GPIO1/GPIO2, GND)",fit
1,J3,5V IN (RAC03),"TerminalBlock_Phoenix_MKDS-1,5-2-5.08_1x02_P5.08mm_Horizontal",5 V from Recom RAC03-05SER/277 flying leads,fit
1,J4,SDC VE1 / GND,"TerminalBlock_Phoenix_MKDS-1,5-2-5.08_1x02_P5.08mm_Horizontal",To SDC X6-6 (VE1) and X5 (GND),fit
1,J5,SDC SERVICE,JST_XH_B4B-XH-A_1x04_P2.50mm_Vertical,"SDC service port: GND_ISO, RX (from SDC TX), TX (to SDC RX), 5 V (VDD_ISO)",fit
1,J6,EXT I/O,PinHeader_1x04_P2.54mm_Vertical,"Expansion header: 3V3, GPIO2, GPIO1, GND",fit
1,J7,USB-C 5V IN,USB_C_Receptacle_GCT_USB4125-xx-x-0190_6P_TopMnt_Horizontal,"5 V input alternative to J3 (any USB-C charger); power sink only, never above 5 V",fit
1,K1,G5V-2-H1 5VDC,Relay_DPDT_Omron_G5V-2,"Fail-safe relay, both poles in parallel; de-energised = R_failsafe",fit
1,PS1,1S4E_0509S1U,Converter_DCDC_TRACO_TME_03xxS_05xxS_12xxS_Single_THT,"Gaptec 1S4E_0509S1U isolated DC/DC 5 V -> 9 V unregulated, 111 mA, 1000 VDC, SIP-4",fit
1,Q1,AO3400A,SOT-23,Relay coil driver,fit
1,Q2,AO3401A,SOT-23,"Reverse-polarity protection: P-FET, gate to GND (Vgs max 12 V), ~25 mV drop",fit
2,R1 R2,2k7,R_0805_2012Metric_Pad1.20x1.40mm_HandSolder,I2C pull-up ESP side (>= 0.5 mA sink current for ISO1540 side 1),fit
1,R10,24k9 0.1% 25ppm,R_Axial_DIN0207_L6.3mm_D2.5mm_P10.16mm_Horizontal,R_failsafe ~20.4 C true = ~20.9 C on the SDC display (+0.5 K offset),fit
1,R11,10k,R_0805_2012Metric_Pad1.20x1.40mm_HandSolder,Relay sense divider: GPIO5 LOW = coil energised,fit
1,R12,20k,R_0805_2012Metric_Pad1.20x1.40mm_HandSolder,Relay sense divider (5 V -> 3.3 V),fit
2,R13 R14,2k2,R_0805_2012Metric_Pad1.20x1.40mm_HandSolder,5 V power LED resistor (~1.3 mA); Relay LED resistor (~1.3 mA),fit
2,R15 R16,1k,R_0805_2012Metric_Pad1.20x1.40mm_HandSolder,"Service RX series resistor (cable protection, limits current on a wrong pinout); Service TX series resistor (limits current if the SDC line also drives)",fit
1,R17,0R,R_0805_2012Metric_Pad1.20x1.40mm_HandSolder,VDD_ISO to the service connector; remove if the SDC port has its own 5 V,fit
2,R20 R21,4k7,R_0805_2012Metric_Pad1.20x1.40mm_HandSolder,Optional pull-up GPIO2 (I2C / 1-Wire); Optional pull-up GPIO1 (I2C / 1-Wire),DNP
2,R22 R23,5k1,R_0805_2012Metric_Pad1.20x1.40mm_HandSolder,"USB-C CC1 Rd: identifies the board as a sink, the charger then supplies 5 V; USB-C CC2 Rd (cable can be plugged either way round)",fit
2,R24 R7,1k5,R_0805_2012Metric_Pad1.20x1.40mm_HandSolder,PS1 preload: the 1S4E needs >= 10 % load (11 mA); 6-7 mA here plus U2/U1/U3/D2 and the LDO's own current; Indicator LED resistor,fit
1,R3,100k,R_0805_2012Metric_Pad1.20x1.40mm_HandSolder,Gate pull-down: relay off while GPIO4 floats,fit
3,R4 R18 R19,100R,R_0805_2012Metric_Pad1.20x1.40mm_HandSolder,Gate series resistor; Series resistor GPIO2 (ESD / short-circuit protection); Series resistor GPIO1 (ESD / short-circuit protection),fit
2,R5 R6,4k7,R_0805_2012Metric_Pad1.20x1.40mm_HandSolder,I2C pull-up SDC side,fit
1,R9,18k2 0.1% 25ppm,R_Axial_DIN0207_L6.3mm_D2.5mm_P10.16mm_Horizontal,R_series: hardware floor ~27 C even if the AD5272 is unpowered or shorted,fit
1,U1,ISO1540,SOIC-8_3.9x4.9mm_P1.27mm,Bidirectional I2C isolator,fit
1,U2,AD5272BRMZ-50,MSOP-10_3x3mm_P0.5mm,"1024-step 50k digital rheostat, I2C address 0x2F (ADDR=GND)",fit
1,U3,ISO7721D,SOIC-8_3.9x4.9mm_P1.27mm,"Service-port UART isolator, 1/1 channels, default output high (UART idle)",fit
1,U4,L78L05,SOT-89-3,"VDD_ISO 5 V from the unregulated ~9-11 V (30 V max input, ~1.7 V dropout)",fit

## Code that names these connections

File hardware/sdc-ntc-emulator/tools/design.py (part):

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    part("R4", "Device:R", "100R", FP_R0805, (76.2, 185.42, 90), {"1": "RELAY_EN", "2": "GATE"},
         Description="Gate series resistor"),
    part("R3", "Device:R", "100k", FP_R0805, (88.9, 193.04, 0), {"1": "GATE", "2": "GND"},
         Description="Gate pull-down: relay off while GPIO4 floats"),
    part("Q1", "Transistor_FET:AO3400A", "AO3400A", "Package_TO_SOT_SMD:SOT-23",
         (101.6, 185.42, 0), {"1": "GATE", "2": "GND", "3": "COIL_N"},
         Description="Relay coil driver"),
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    ("ESP DOMAIN (earthed via USB/PC allowed)", (20.32, 15.24), 2.5),
    ("ISOLATED SDC DOMAIN (referenced to SDC X5 only)", (195.58, 15.24), 2.5),
    ("DevKit: ESP32-S3-DevKitC-1 (N16R8 clone), header rows 25.1 mm apart (measured).\n"
     "GPIO4 = RELAY_EN (ESPHome restore_mode ALWAYS_OFF), GPIO5 = RELAY_SENSE (LOW = coil on),\n"
     "GPIO8 = SDA, GPIO9 = SCL, GPIO6 = service RX, GPIO7 = service TX (UART),\n"
     "GPIO1/GPIO2 = expansion header J6.", (20.32, 228.6), 1.5),
    ("SDC service port (J5): UART at 5 V logic, isolated by U3. Pinout of the SDC socket\n"
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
